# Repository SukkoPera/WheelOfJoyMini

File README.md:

# WheelOfJoyMini
WheelOfJoyMini is an Open Hardware 4-player joystick adapter for the Commodore 16, 116 and Plus/4 with 2-button support.

## Summary
After I released [WheelOfJoy](https://github.com/SukkoPera/WheelOfJoy), some people suggested that a 4-player adapter with support for 2 joystick buttons would probably be more useful, so here we go :).

Just like its bigger brother, the board plugs in the User Port, which means that in order to use it on a C16 or C116, you will need [a User Port card](https://github.com/SukkoPera/16up).

## Assembly
I recommend soldering all the resistor arrays first, then the chips and the capacitors, with the ports last.

The adapter can be connected to the computer through a cable with a User Port connector on one side and a male DB-15 on the other. I did this so that the adapter can be placed more freely on the table so that all players can reach it comfortably. The adapter-end of the cable can also be soldered directly to it, if you prefer. Pin names are noted on the board, but here's a handy table:

| DB-15 Pin # | Signal | User Port Pin # | Notes                  |
|-------------|--------|-----------------|------------------------|
|1	          | +5V    | 2               |                        |
|2	          | P0     | B               |                        |
|3	          | P1     | K               |                        |
|4	          | P2     | 4               |                        |
|5	          | P3     | 5               |                        |
|6	          | /RESET | 3               | Not used by this board |
|7	          | +9V    | 10              | Not used by this board |
|8	          | GND    | 1, 12, A or N   |                        |
|9	          | +5V    | 2               |                        |
|10	          | P4     | 6               |                        |
|11	          | P5     | 7               |                        |
|12	          | P6     | J               |                        |
|13	          | P7     | F               |                        |
|14	          | -9V    | 11              | Not used by this board |
|15	          | GND    | 1, 12, A or N   |                        |

This is exactly the same cable used by WheelOfJoy.

[This](https://www.thingiverse.com/thing:3368773) and [these](https://www.thingiverse.com/thing:5213203) will help you make a good-looking job with your cable.

I estimate all the components required to self-build this thing to cost < 10€, probably closer to 5€ if you get them from China.

## Supported Games
Of course there isn't any software support for this at the moment. It's up to the developers to write party games for the C16/+4 for up to 6 players!

## Programming
The board uses 3 dual 4-to-1 multiplexers, totalling to 6 multiplexers: one per direction plus one for every fire button. Channel selection happens in parallel on all multiplexers and is done with the 2 high bits of the User Port.

1. Write a value N at the User Port register depending on the port you want to read. General formula for port P ∈ [1,4] is the following:

   ```N = ((P - 1) << 6) | 0x3F```

   Or just pick your value from the following table:

   | # | Binary    | Hex| Dec |
   |---|-----------|----|-----|
   | 1 | 00 111111 | 3F |  63 |
   | 2 | 01 111111 | 7F | 127 |
   | 3 | 10 111111 | BF | 191 |
   | 4 | 11 111111 | FF | 255 |

2. Read the value of the User Port register, the lower 6 bits will report direction/button status:

   | Bit 7 | Bit 6 | Bit 5  | Bit 4  | Bit 3 | Bit 2 | Bit 1 | Bit 0 |
   |-------|-------|--------|--------|-------|-------|-------|-------|
   |   X   |   X   |Button 2|Button 1| Left  | Right | Down  | Up    |

   Every bit will be 0 if the corresponding direction/button is pressed, 1 otherwise.

## Compatibility
Any Atari-compliant joystick or joypad should work with this board. Button 2 is expected to be wired to pin 9 and to be active-low as all the other buttons. This is the most common setup, used by all 2-button joysticks and adapters designed for the Amiga, including [my PSX adapter](https://github.com/SukkoPera/OpenPSX2AmigaPadAdapter) and the [my variant of the Unijoysticle2](https://gitlab.com/SukkoPera/unijoysticle2).

Sega controllers also use the same configuration: you can use Master System and Mega Drive/Genesis - buttons B and C - controllers straight away as **the adapter also provides power to pin 5**.

The latter also means that you MUST NOT use the adapter with anything that can pull pin 5 straight to ground, such as 3-button Amiga mice (what would be the purpose of that anyway?).

Note that the few 2-button games for the C64 typically use inverted logic for button 2 (don't ask me why but this dates back to the C64 GS, I think), even if this was handled in SW, I cannot guarantee that any joysticks made this way will work correctly with the adapter.

Also keep in mind that the User Port is only guaranteed to provide 100 mA on the +5V pin, even though I don't think there's anything actually limiting that.

## Releases
If you want to get this board produced, you are recommended to get [the latest release](https://github.com/SukkoPera/WheelOfJoyMini/releases) rather than the current git version, as the latter might be under development and is not guaranteed to be working.

Every release is accompanied by its Bill Of Materials (BOM) file and any relevant notes about it, which you are recommended to read carefully.

## License
The WheelOfJoyMini documentation, including the design itself, is copyright &copy; SukkoPera 2019-2021 and is licensed under the [Creative Commons Attribution-NonCommercial-ShareAlike 4.0 International License](https://creativecommons.org/licenses/by-nc-sa/4.0/).

This documentation is distributed *as is* and WITHOUT ANY EXPRESS OR IMPLIED WARRANTIES whatsoever with respect to its functionality, operability or use, including, without limitation, any implied warranties OF MERCHANTABILITY, SATISFACTORY QUALITY, FITNESS FOR A PARTICULAR PURPOSE or infringement. We expressly disclaim any liability whatsoever for any direct, indirect, consequential, incidental or special damages, including, without limitation, lost revenues, lost profits, losses resulting from business interruption or loss of data, regardless of the form of action or legal theory under which the liability may be asserted, even if advised of the possibility or likelihood of such damages.

## Support the Project
If you want to get some boards manufactured, you can get them from PCBWay through this link:

You get my gratitude and cheap, professionally-made and good quality PCBs, I get some credit that will help with this and [other projects](https://www.pcbway.com/project/member/shareproject/?bmbid=41100). You won't even have to worry about the various PCB options, it's all pre-configured for you!

Also, if you still have to register, [you can use this link](https://www.pcbway.com/setinvite.aspx?inviteid=41100) to get some bonus initial credit (and yield me some more).

You can also buy me a coffee if you want:

## Credits
* Thanks to siz for the idea.
* Thanks to Solder for being such a prolific hacker and a great inspiration :).
* 3D model of [DB-9](https://grabcad.com/library/d-sub-9-pin-male-1) and [DB-15 connector](https://grabcad.com/library/d-sub-15-pin-female-2-lines-1) by Alex K.
* Font used for port numbers is [Agreement Signature by wepfont](https://www.fontspace.com/a-agreement-signature-font-f52534) (800 DPI).
* Font used for the logo is [Senja Santuy by Zuzulgo](https://www.fontspace.com/senja-santuy-font-f74971) (450 DPI).

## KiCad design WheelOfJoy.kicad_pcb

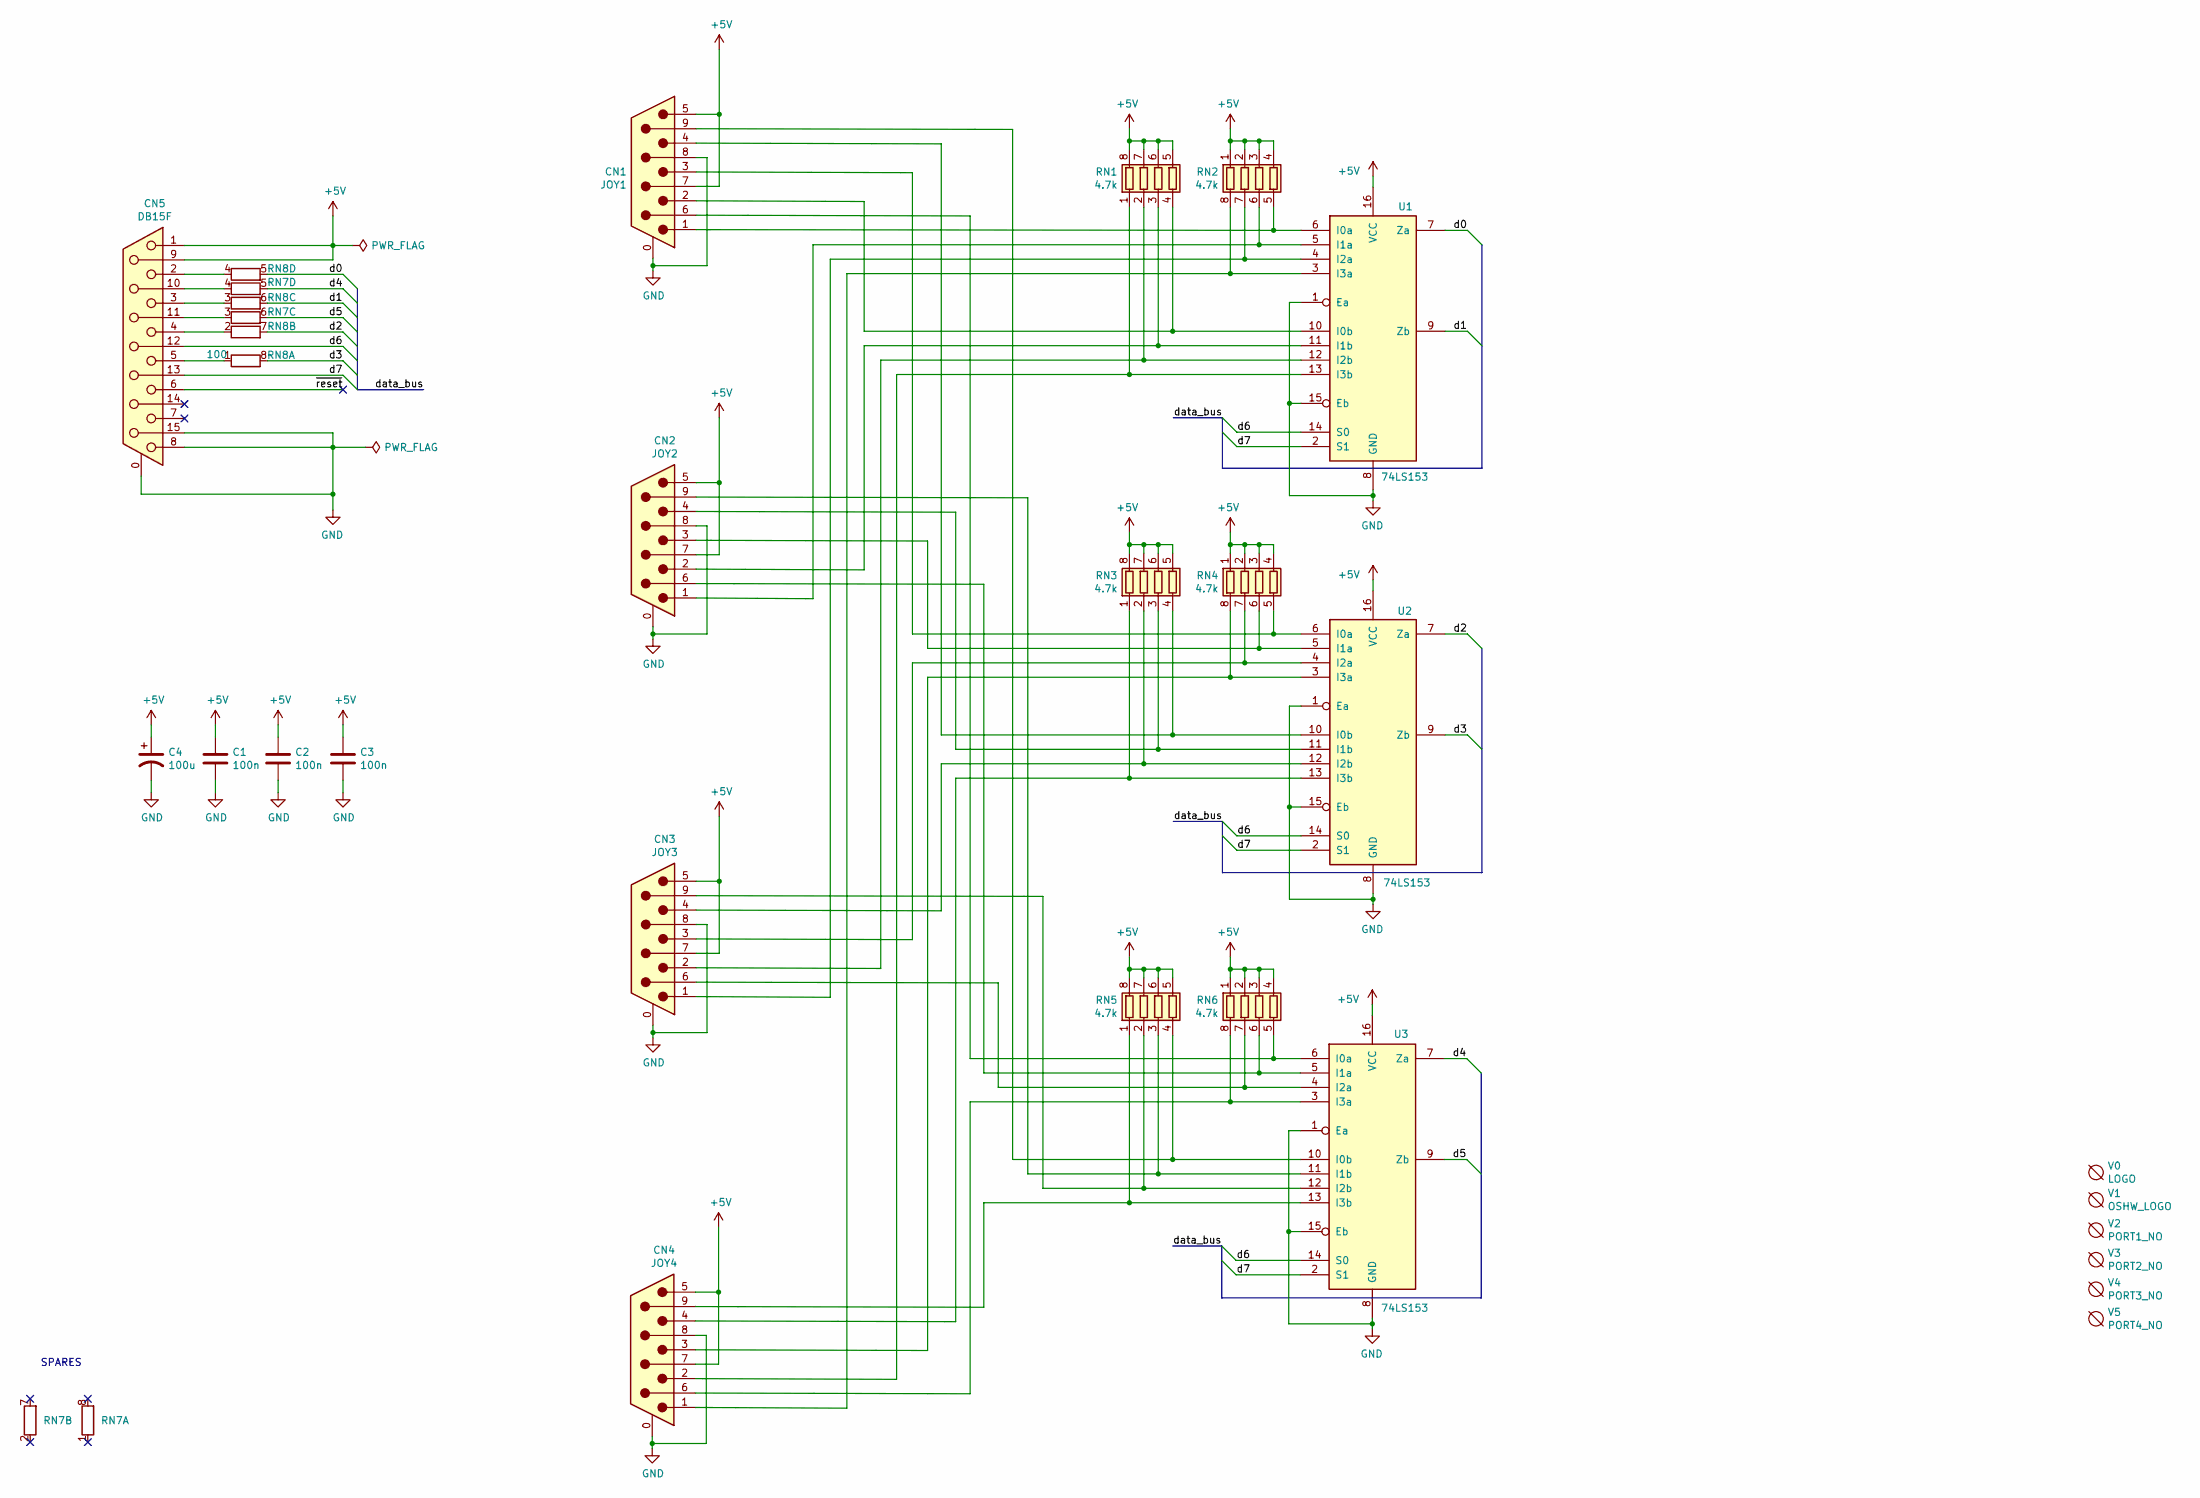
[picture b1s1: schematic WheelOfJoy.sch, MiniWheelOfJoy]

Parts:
C1, C2, C3: 100n; C_0805_2012Metric_Pad1.18x1.45mm_HandSolder
C4: 100u; CP_EIA-7343-30_AVX-N_Pad2.25x2.55mm_HandSolder
CN1: JOY1; DSUB-9_Male_EdgeMount_P2.77mm
CN2: JOY2; DSUB-9_Male_EdgeMount_P2.77mm
CN3: JOY3; DSUB-9_Male_EdgeMount_P2.77mm
CN4: JOY4; DSUB-9_Male_EdgeMount_P2.77mm
CN5: DB15F; DSUB-15_Female_EdgeMount_P2.77mm
RN1, RN2, RN3, RN4, RN5, RN6: 4.7k; R_Array_Convex_4x0603
RN7, RN8: 100; R_Array_Convex_4x0603
U1, U2, U3: 74LS153; SOIC-16_3.9x9.9mm_P1.27mm
V0: LOGO; logo
V1: OSHW_LOGO; cc_by_nc_sa
V2: PORT1_NO; port1
V3: PORT2_NO; port2
V4: PORT3_NO; port3
V5: PORT4_NO; port4

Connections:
+5V: C1.1, C2.1, C3.1, C4.1, CN1.5, CN1.7, CN2.5, CN2.7, CN3.5, CN3.7, CN4.5, CN4.7, CN5.1, CN5.9, RN1.5 (R4.2), RN1.6 (R3.2), RN1.7 (R2.2), RN1.8 (R1.2), RN2.1 (R1.1), RN2.2 (R2.1), RN2.3 (R3.1), RN2.4 (R4.1), RN3.5 (R4.2), RN3.6 (R3.2), RN3.7 (R2.2), RN3.8 (R1.2), RN4.1 (R1.1), RN4.2 (R2.1), RN4.3 (R3.1), RN4.4 (R4.1), RN5.5 (R4.2), RN5.6 (R3.2), RN5.7 (R2.2), RN5.8 (R1.2), RN6.1 (R1.1), RN6.2 (R2.1), RN6.3 (R3.1), RN6.4 (R4.1), U1.16 (VCC), U2.16 (VCC), U3.16 (VCC)
/d0: RN8.5 (R4.2), U1.7 (Za)
/d1: RN8.6 (R3.2), U1.9 (Zb)
/d2: RN8.7 (R2.2), U2.7 (Za)
/d3: RN8.8 (R1.2), U2.9 (Zb)
/d4: RN7.5 (R4.2), U3.7 (Za)
/d5: RN7.6 (R3.2), U3.9 (Zb)
/d6: CN5.12, U1.14 (S0), U2.14 (S0), U3.14 (S0)
/d7: CN5.13, U1.2 (S1), U2.2 (S1), U3.2 (S1)
/~reset: CN5.6
GND: C1.2, C2.2, C3.2, C4.2, CN1.0 (PAD), CN1.8, CN2.0 (PAD), CN2.8, CN3.0 (PAD), CN3.8, CN4.0 (PAD), CN4.8, CN5.0 (PAD), CN5.8, CN5.15, U1.1 (Ea), U1.8 (GND), U1.15 (Eb), U2.1 (Ea), U2.8 (GND), U2.15 (Eb), U3.1 (Ea), U3.8 (GND), U3.15 (Eb)
unnamed: CN1.1, RN2.5 (R4.2), U1.6 (I0a)
unnamed: CN1.2, RN1.4 (R4.1), U1.10 (I0b)
unnamed: CN1.3, RN4.5 (R4.2), U2.6 (I0a)
unnamed: CN1.4, RN3.4 (R4.1), U2.10 (I0b)
unnamed: CN1.6, RN6.5 (R4.2), U3.6 (I0a)
unnamed: CN1.9, RN5.4 (R4.1), U3.10 (I0b)
unnamed: CN2.1, RN2.6 (R3.2), U1.5 (I1a)
unnamed: CN2.2, RN1.3 (R3.1), U1.11 (I1b)
unnamed: CN2.3, RN4.6 (R3.2), U2.5 (I1a)
unnamed: CN2.4, RN3.3 (R3.1), U2.11 (I1b)
unnamed: CN2.6, RN6.6 (R3.2), U3.5 (I1a)
unnamed: CN2.9, RN5.3 (R3.1), U3.11 (I1b)
unnamed: CN3.1, RN2.7 (R2.2), U1.4 (I2a)
unnamed: CN3.2, RN1.2 (R2.1), U1.12 (I2b)
unnamed: CN3.3, RN4.7 (R2.2), U2.4 (I2a)
unnamed: CN3.4, RN3.2 (R2.1), U2.12 (I2b)
unnamed: CN3.6, RN6.7 (R2.2), U3.4 (I2a)
unnamed: CN3.9, RN5.2 (R2.1), U3.12 (I2b)
unnamed: CN4.1, RN2.8 (R1.2), U1.3 (I3a)
unnamed: CN4.2, RN1.1 (R1.1), U1.13 (I3b)
unnamed: CN4.3, RN4.8 (R1.2), U2.3 (I3a)
unnamed: CN4.4, RN3.1 (R1.1), U2.13 (I3b)
unnamed: CN4.6, RN6.8 (R1.2), U3.3 (I3a)
unnamed: CN4.9, RN5.1 (R1.1), U3.13 (I3b)
unnamed: CN5.2, RN8.4 (R4.1)
unnamed: CN5.3, RN8.3 (R3.1)
unnamed: CN5.4, RN8.2 (R2.1)
unnamed: CN5.5, RN8.1 (R1.1)
unnamed: CN5.10, RN7.4 (R4.1)
unnamed: CN5.11 (P111), RN7.3 (R3.1)

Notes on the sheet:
SPARES

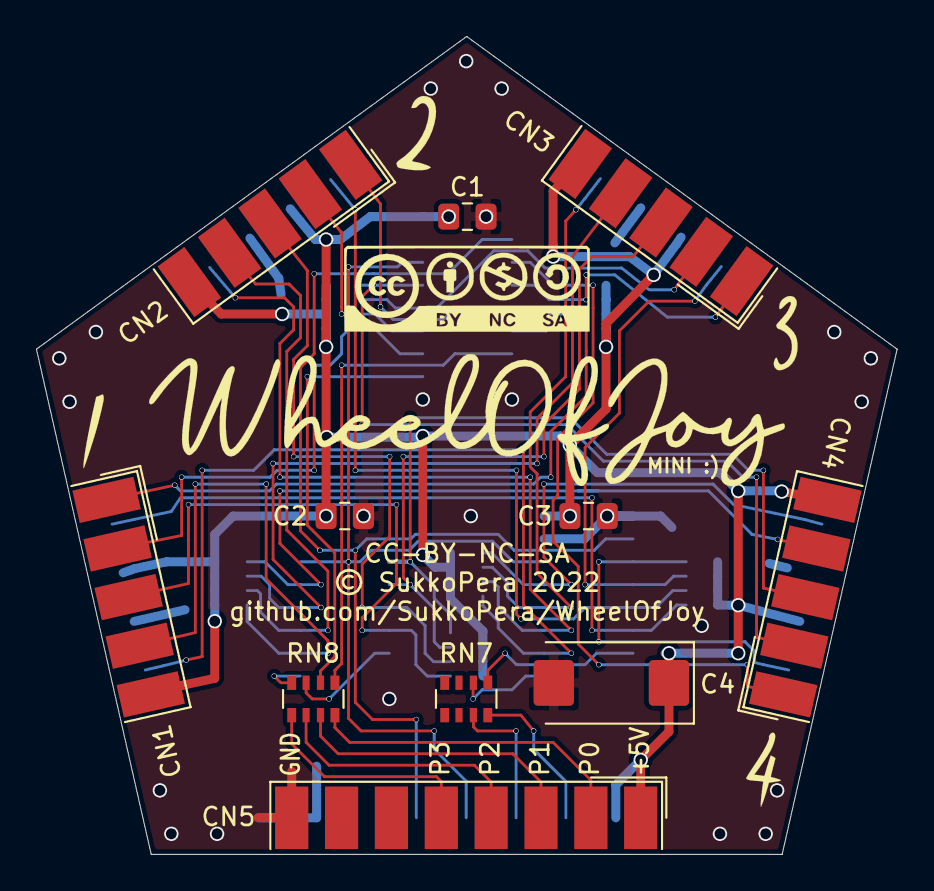
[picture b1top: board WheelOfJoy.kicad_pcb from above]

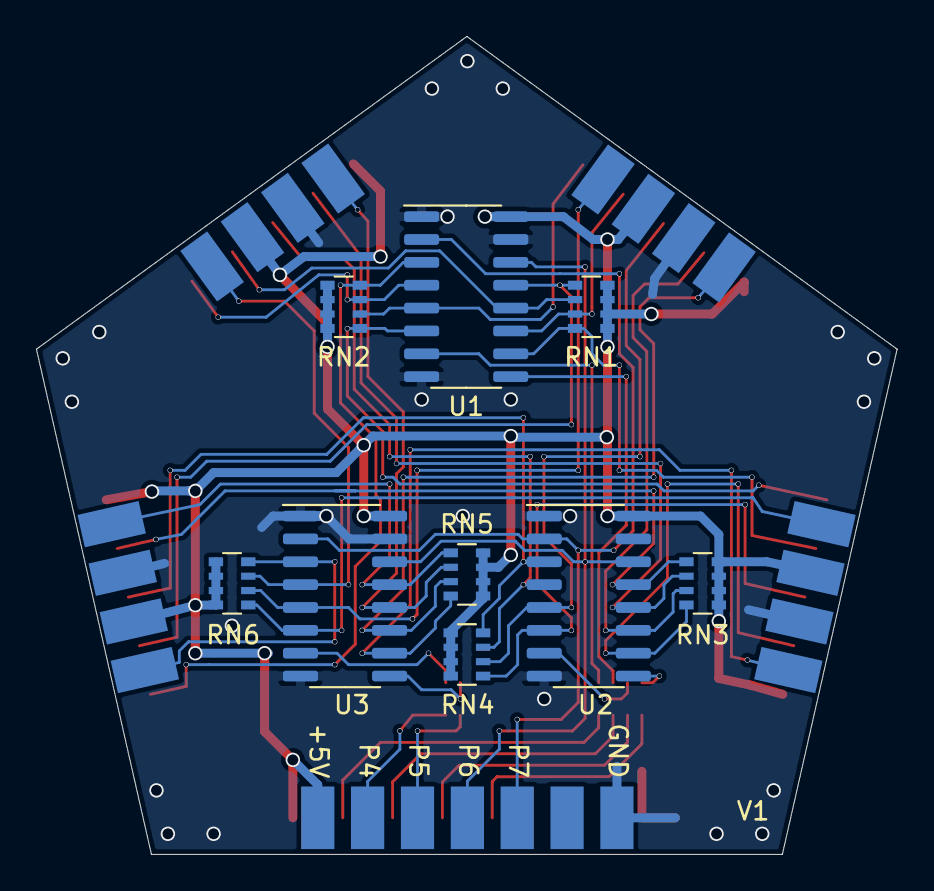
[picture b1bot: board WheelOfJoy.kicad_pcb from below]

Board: 2 copper layers, 47.8 x 45.4 mm, 26 parts (9 on the bottom side), 40 nets.

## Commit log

2022-12-03 Import WOJ repo
2022-12-03 Almost there
2022-12-03 Honing tracks
2022-12-03 Another one
2022-12-03 Another port done
2022-12-03 Restart routing from scratch
2022-12-03 Update silkscreen
2022-12-04 Last port done
2022-12-04 YEAH!
2023-01-17 Update renders and README
2023-01-17 Update board link
2023-01-17 Add sponsor link

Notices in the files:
WheelOfJoy.kicad_pcb:
© SukkoPera 2022
